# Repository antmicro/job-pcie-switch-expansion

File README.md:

# PCIe Switch Expansion for Antmicro Baseboard for NVIDIA Jetson Orin

Copyright (c) 2026 [Antmicro](https://www.antmicro.com)

## Overview

This project contains open hardware PCB design files for an expansion board compatible with Antmicro's [Baseboard for Jetson Orin](https://github.com/antmicro/jetson-orin-baseboard).
The design includes a PCIe 3.0 switch that expands the number of available PCIe ports by connecting multiple PCIe endpoint devices to a single PCIe root complex.
The expansion board includes an OCuLink Connector and two M.2 (key-M) slots intended for connecting additional storage solutions with optional RAID support.
Both M.2 slots support 2280 and 2242 M.2 NVMe drives.
The design files were prepared in KiCad 10.x.

## Key features

* Accessory compatible with expansion connector located on Antmicro Baseboard NVIDIA Jetson Orin
* Supports for 2280 and 2242 M.2 NVMe drives
* 1x M.2 key M PCIe x2 slot 
* 1x M.2 key M or 1x OCuLink Connector PCIe x2 (multiplexed lane)
* 100 x 60 mm (3.94 x 2.36 inch) PCB outline

## Project structure 

The main directory contains KiCad PCB project files, the LICENSE, and this README, and the img directory contains graphics for this README.

## Licensing

This project is published under the [Apache-2.0](LICENSE) license.

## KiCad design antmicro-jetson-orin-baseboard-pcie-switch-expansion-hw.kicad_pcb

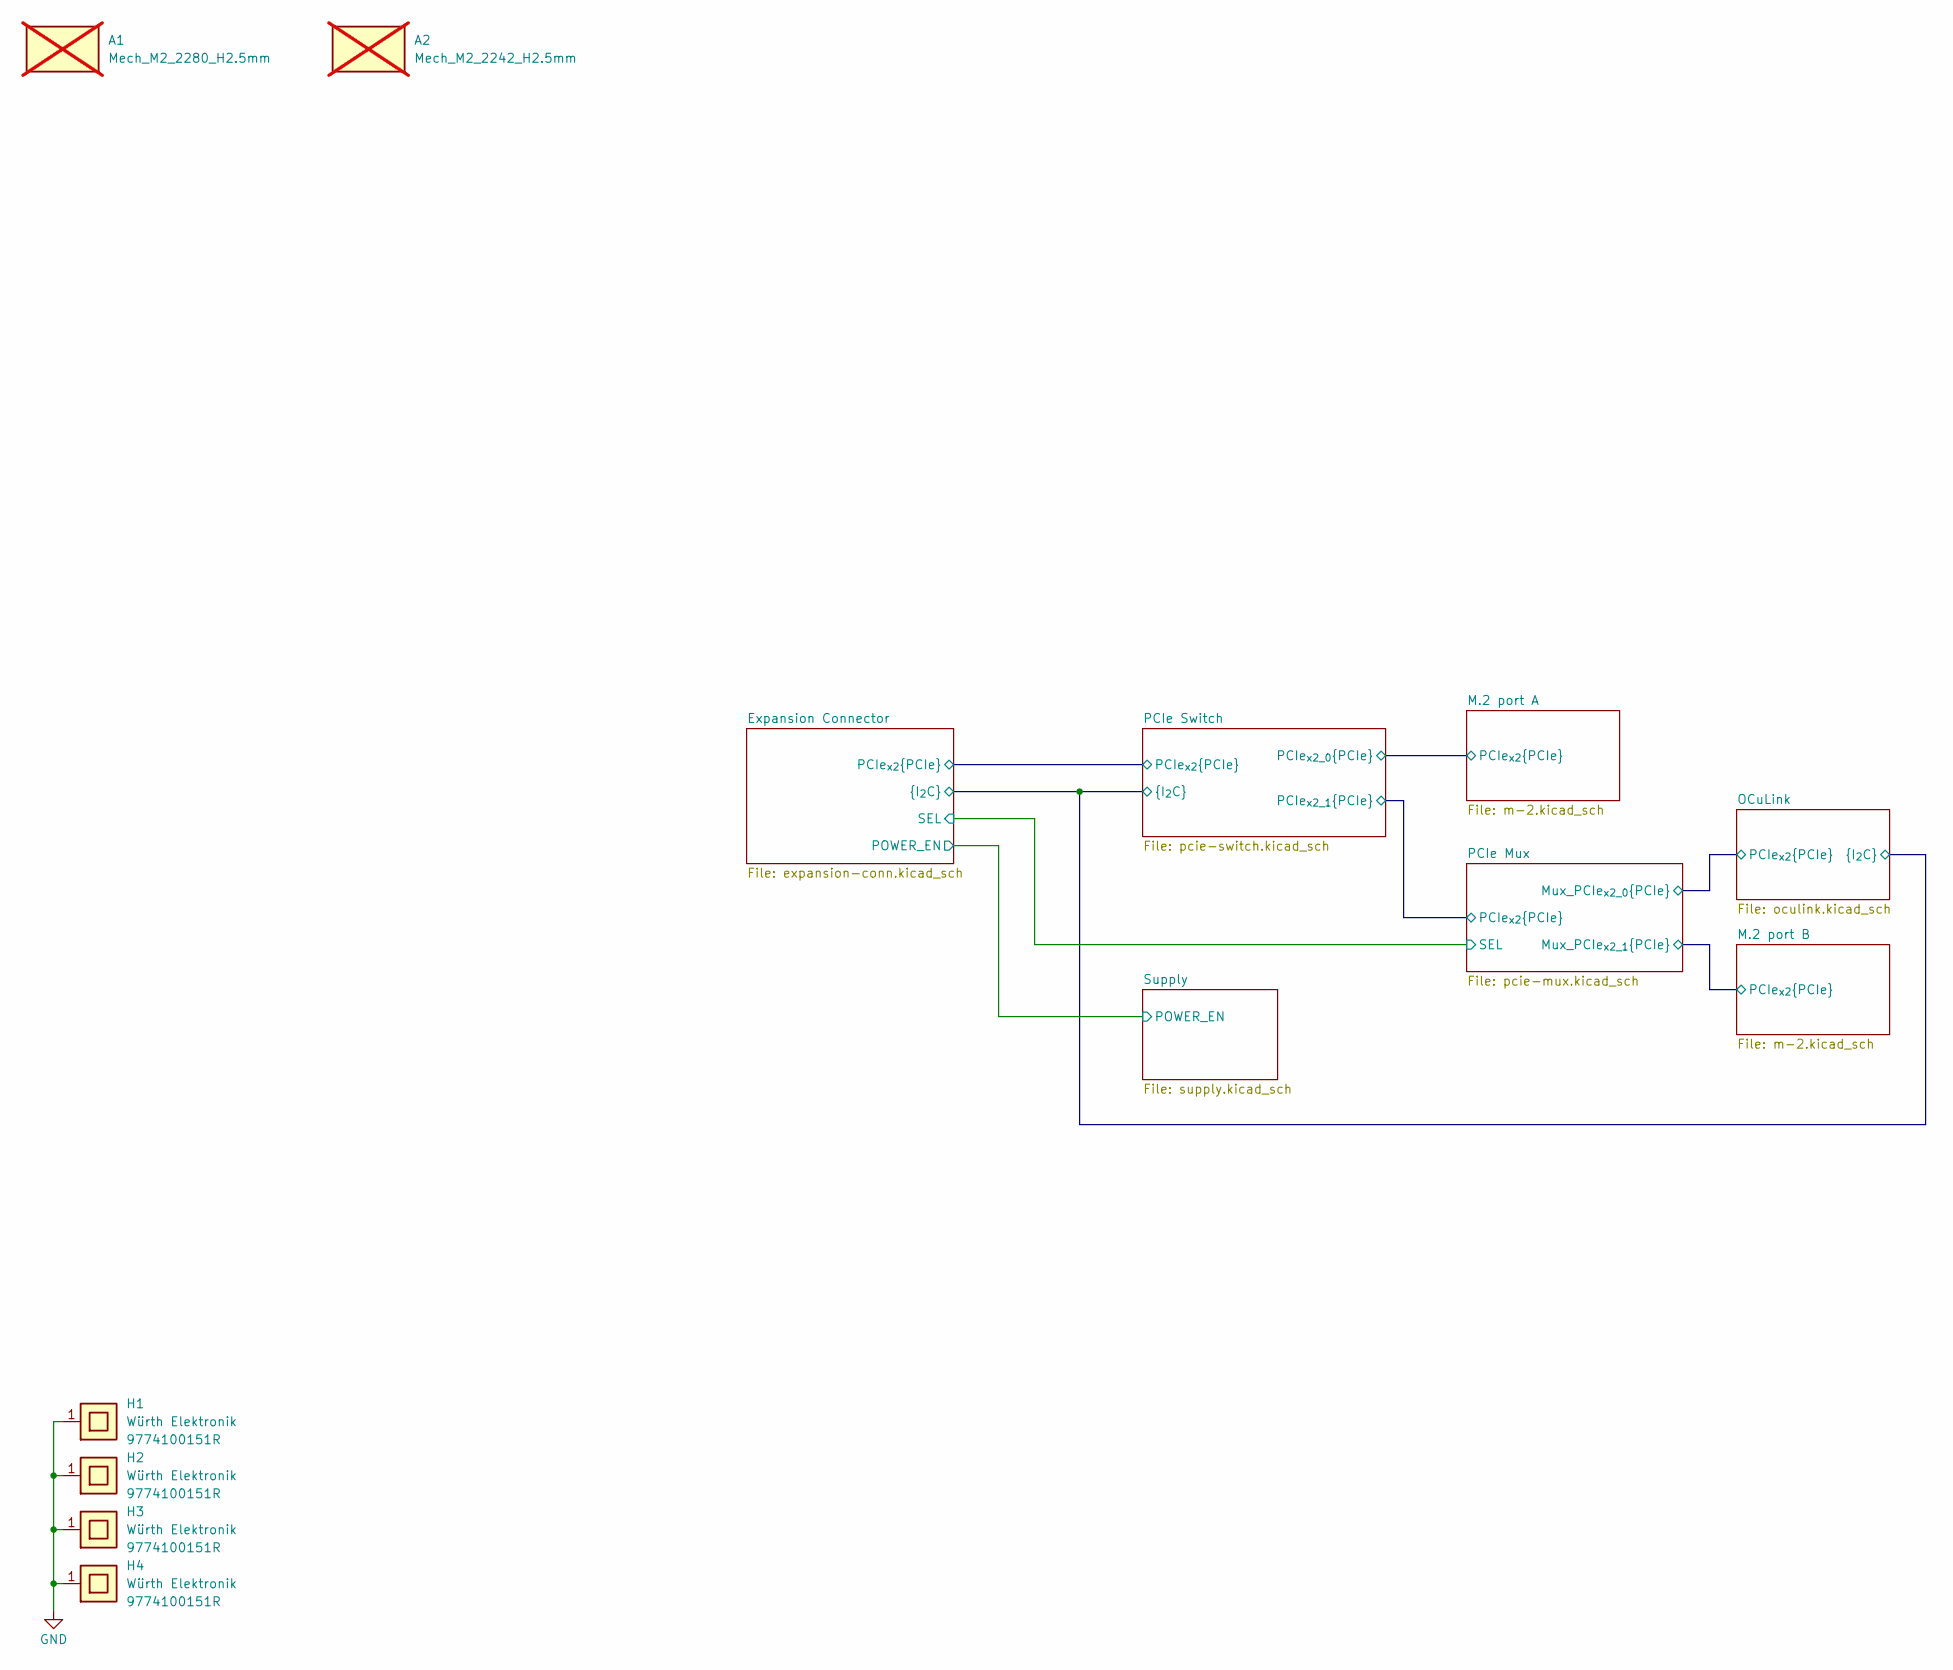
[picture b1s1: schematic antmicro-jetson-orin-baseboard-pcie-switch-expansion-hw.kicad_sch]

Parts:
A1: Mech_M2_2280_H2.5mm; not fitted
A2: Mech_M2_2242_H2.5mm; not fitted
H1, H2, H3, H4: Spacer_Drill3.7mm_H10mm_9774100151R; MPN 9774100151R

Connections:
GND: H1.1, H2.1, H3.1, H4.1; also elsewhere on the board

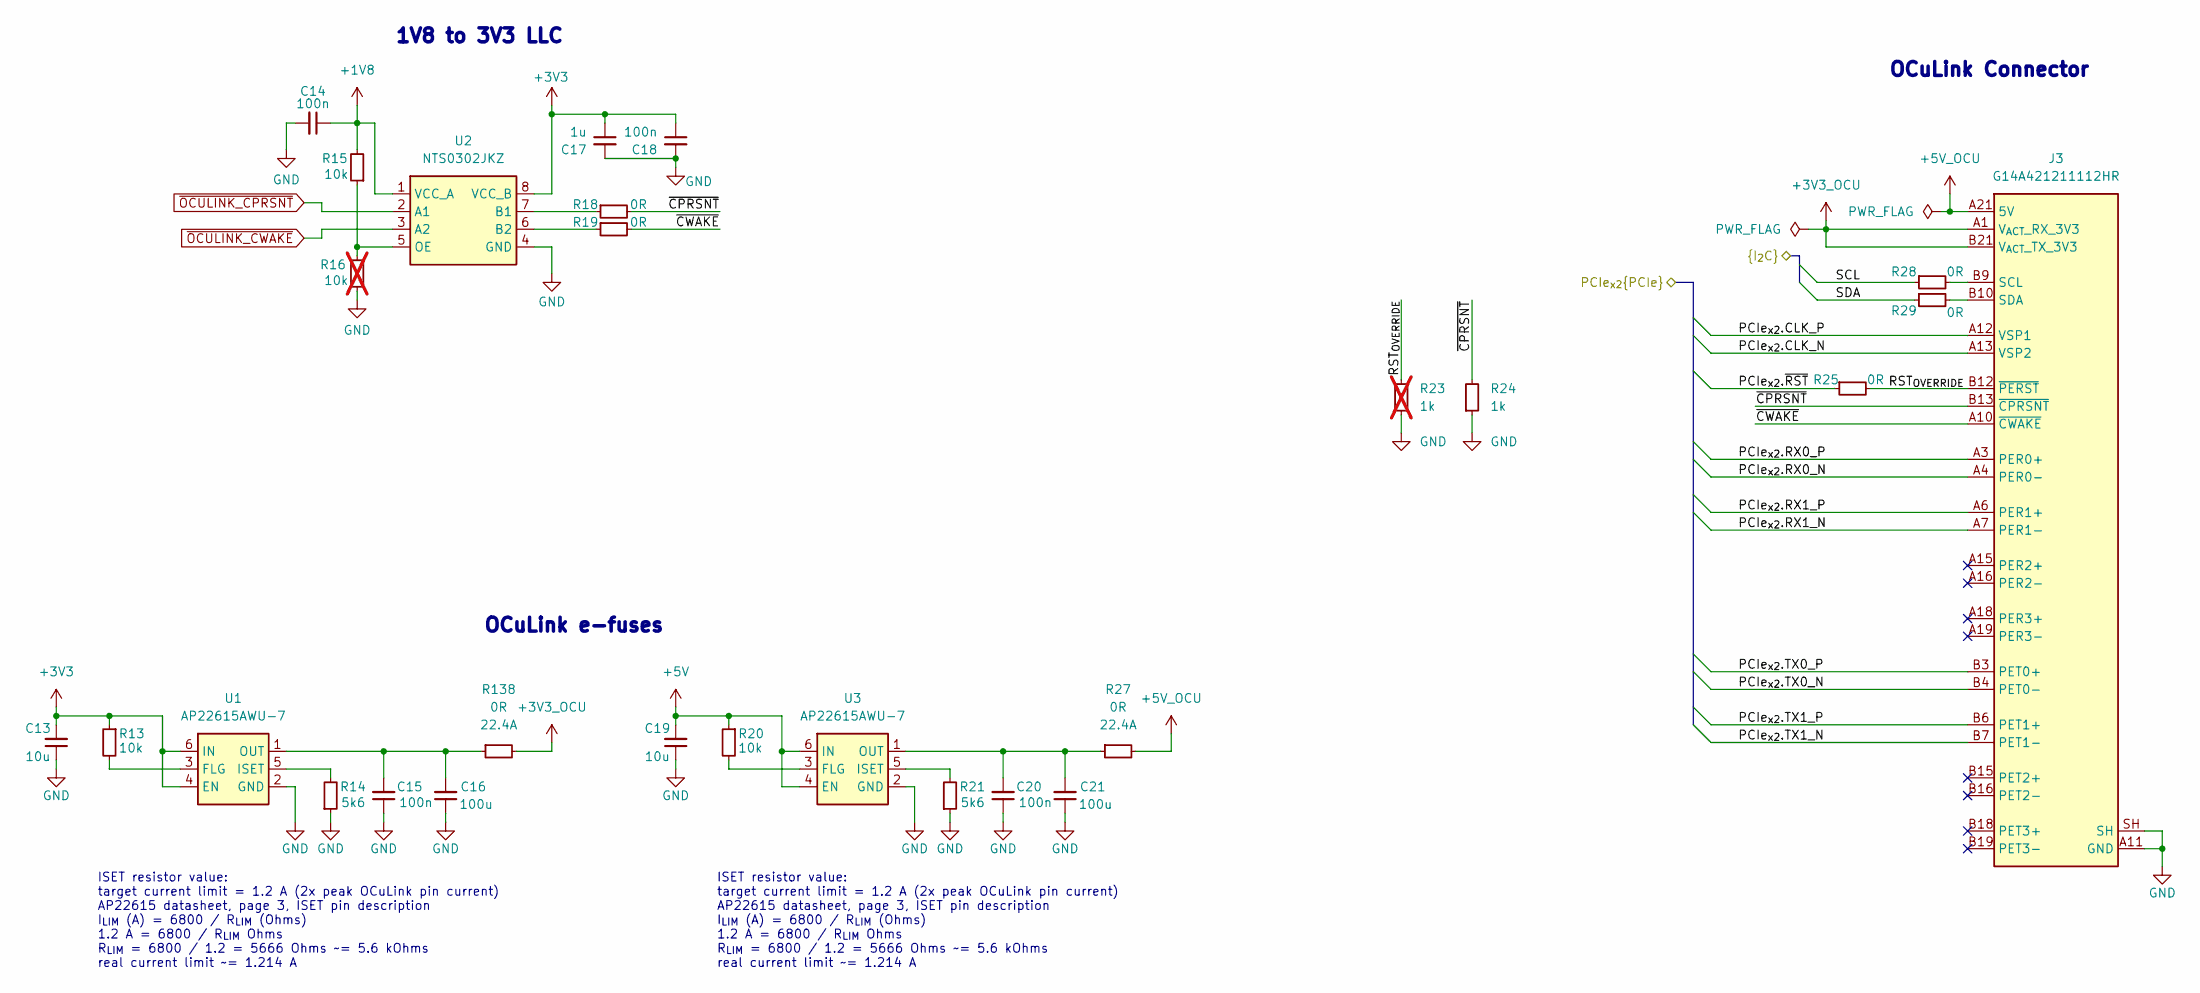
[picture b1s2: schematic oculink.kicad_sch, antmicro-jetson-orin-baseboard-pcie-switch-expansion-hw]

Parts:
C13, C19: C_10u_0402; C_0402_1005Metric; MPN CC0402MRX5R5BB106
C14, C15, C18, C20: C_100n_0402; C_0402_1005Metric; Voltage 50V; MPN GRM155R61H104KE14D
C16, C21: C_100u_0805; C_0805_2012Metric; MPN GRM21BR60J107ME15L
C17: C_1u_0402; C_0402_1005Metric; MPN C1005X6S1A105K050BC
J3: OCuLink_x4_Amphenol_G14A421211112HR; Amphenol_G14A421211112HR; MPN G14A421211112HR
R13, R15, R20: R_10k_0402; R_0402_1005Metric; Tolerance 1%; MPN CR0402-FX-1002GLF
R14, R21: R_5k6_0402; R_0402_1005Metric; Tolerance 1%; MPN CR0402-FX-5601GLF
R16: R_10k_0402; R_0402_1005Metric; Tolerance 1%; MPN CR0402-FX-1002GLF; not fitted
R18, R19, R25, R28, R29: R_0R_0402; R_0402_1005Metric; MPN ERJ2GE0R00X
R23: R_1k_0402; R_0402_1005Metric; Tolerance 1%; MPN CR0402-FX-1001GLF; not fitted
R24: R_1k_0402; R_0402_1005Metric; Tolerance 1%; MPN CR0402-FX-1001GLF
R27, R138: R_0R_22.4A_0603; R_0603_1608Metric; Tolerance template_tolerance; MPN PMR03EZPJ000
U1, U3: TSOT23-6; MPN AP22615AWU-7
U2: NTS0302JKZ; X2SON8_1.4x1x0.32mm_P0.35mm; MPN NTS0302JKZ

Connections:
+1V8: C14.1, R15.2, U2.1 (VCC_A); also elsewhere on the board
+3V3: C13.2, C17.1, C18.1, R13.1, U1.4 (EN), U1.6 (IN), U2.8 (VCC_B); also elsewhere on the board
+3V3_OCU: J3.A1 (V_{ACT}_RX_3V3), J3.B21 (V_{ACT}_TX_3V3), R138.2
+5V: C19.2, R20.1, U3.4 (EN), U3.6 (IN); also elsewhere on the board
+5V_OCU: J3.A21 (5V), J3.B1 (5V), R27.2
/Expansion Connector/SCL: R28.1; also elsewhere on the board
/Expansion Connector/SDA: R29.1; also elsewhere on the board
/OCuLink/PCIe_{x2}.CLK_N: J3.A13 (VSP2); also elsewhere on the board
/OCuLink/PCIe_{x2}.CLK_P: J3.A12 (VSP1); also elsewhere on the board
/OCuLink/PCIe_{x2}.RX0_N: J3.A4 (PER0-); also elsewhere on the board
/OCuLink/PCIe_{x2}.RX0_P: J3.A3 (PER0+); also elsewhere on the board
/OCuLink/PCIe_{x2}.RX1_N: J3.A7 (PER1-); also elsewhere on the board
/OCuLink/PCIe_{x2}.RX1_P: J3.A6 (PER1+); also elsewhere on the board
/OCuLink/PCIe_{x2}.TX0_N: J3.B4 (PET0-); also elsewhere on the board
/OCuLink/PCIe_{x2}.TX0_P: J3.B3 (PET0+); also elsewhere on the board
/OCuLink/PCIe_{x2}.TX1_N: J3.B7 (PET1-); also elsewhere on the board
/OCuLink/PCIe_{x2}.TX1_P: J3.B6 (PET1+); also elsewhere on the board
/OCuLink/PCIe_{x2}.~RST: R25.1; also elsewhere on the board
/OCuLink/RST_{OVERRIDE}: J3.B12 (~PERST), R23.2, R25.2
/OCuLink/~CPRSNT: J3.B13 (~CPRSNT), R18.2, R24.2
/OCuLink/~CWAKE: J3.A10 (~CWAKE), R19.2
GND: C13.1, C14.2, C15.1, C16.1, C17.2, C18.2, C19.1, C20.1, C21.1, J3.A2 (GND), J3.A5 (GND), J3.A8 (GND), J3.A11 (GND), J3.A14 (GND), J3.A17 (GND), J3.A20 (GND), J3.B2 (GND), J3.B5 (GND), J3.B8 (GND), J3.B11 (GND), J3.B14 (GND), J3.B17 (GND), J3.B20 (GND), J3.SH, R14.1, R16.1, R21.1, R23.1, R24.1, U1.2 (GND), U2.4 (GND), U3.2 (GND); also elsewhere on the board
unnamed: J3.B9 (SCL), R28.2
unnamed: J3.B10 (SDA), R29.2
unnamed: R13.2, U1.3 (FLG)
unnamed: R14.2, U1.5 (ISET)
unnamed: C15.2, C16.2, R138.1, U1.1 (OUT)
unnamed: R18.1, U2.7 (B1)
unnamed: R19.1, U2.6 (B2)
unnamed: R15.1, R16.2, U2.5 (OE)
unnamed: R20.2, U3.3 (FLG)
unnamed: R21.2, U3.5 (ISET)
unnamed: C20.2, C21.2, R27.1, U3.1 (OUT)
~OCULINK_CPRSNT: U2.2 (A1); also elsewhere on the board
~OCULINK_CWAKE: U2.3 (A2); also elsewhere on the board

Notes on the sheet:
ISET resistor value: target current limit = 1.2 A (2x peak OCuLink pin current) AP22615 datasheet, page 3, ISET pin description I_{LIM} (A) = 6800 / R_{LIM} (Ohms) 1.2 A = 6800 / R_{LIM} Ohms R_{LIM} = 6800 / 1.2 = 5666 Ohms ~= 5.6 kOhms real current limit ~= 1.214 A
OCuLink e-fuses
1V8 to 3V3 LLC
OCuLink Connector

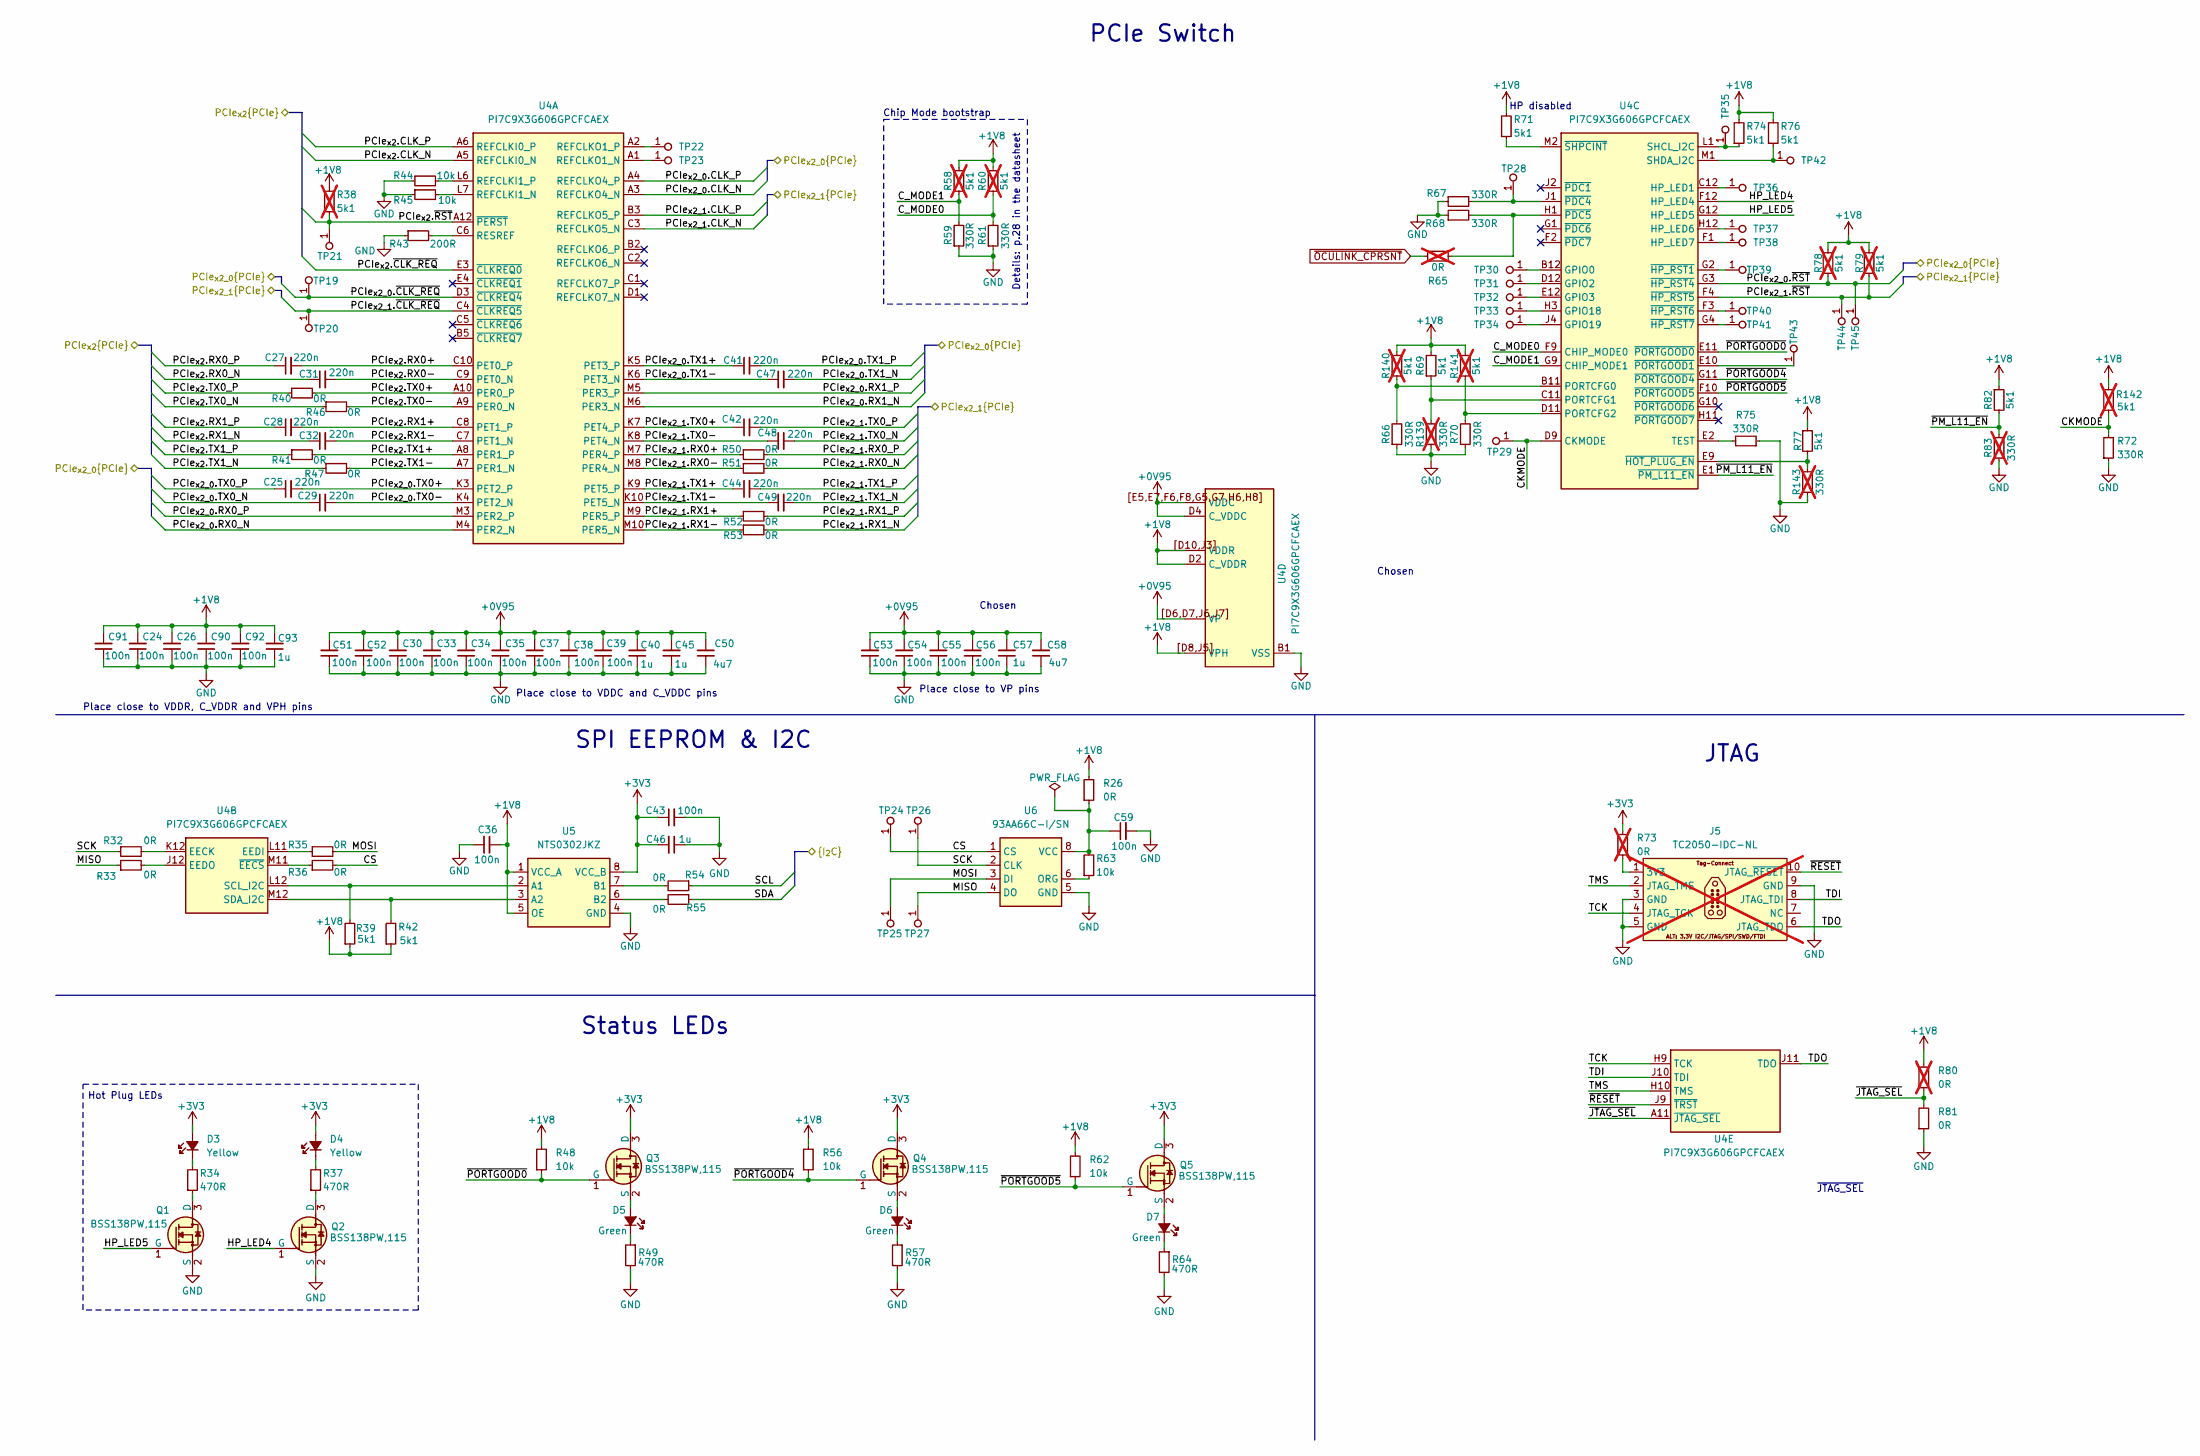
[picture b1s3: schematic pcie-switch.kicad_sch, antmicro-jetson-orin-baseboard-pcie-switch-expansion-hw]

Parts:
C24, C26, C30, C33, C34, C35, C36, C37, C38, C39, C43, C51, C52, C53, C54, C55, C56, C59, C90, C91, C92: C_100n_0402; C_0402_1005Metric; Voltage 50V; MPN GRM155R61H104KE14D
C25, C27, C28, C29, C31, C32, C41, C42, C44, C47, C48, C49: C_220n_0402; C_0402_1005Metric; MPN CC0402KRX5R6BB224
C40, C45, C46, C57, C93: C_1u_0402; C_0402_1005Metric; MPN C1005X6S1A105K050BC
C50, C58: C_4u7_25V_0402; C_0402_1005Metric; Voltage 25V; MPN GRM155C61E475ME15J
D3, D4: LED_Y_0402_VLMY1500-GS08; LED_0402_1005Metric_Y; MPN VLMY1500-GS08
D5, D6, D7: LED_G_0603_LG_L29K-G2J1-24-Z; LED_0603_1608Metric_G; MPN LG L29K-G2J1-24-Z
J5: Tag-Connect_TC2050-IDC-NL_2x5_P1.27mm; MPN TC2050-IDC-NL; not fitted
Q1, Q2, Q3, Q4, Q5: BSS138PW,115; SC70-3; MPN BSS138PW,115
R26, R32, R33, R35, R36, R40, R41, R46, R47, R50, R51, R52, R53, R54, R55, R81: R_0R_0402; R_0402_1005Metric; MPN ERJ2GE0R00X
R34, R37, R49, R57, R64: R_470R_0402; R_0402_1005Metric; Tolerance 1%; MPN CR0402-FX-4700GLF
R38, R58, R60, R78, R79, R140, R141, R142: R_5k1_0402; R_0402_1005Metric; Tolerance 1%; MPN CR0402-FX-5101GLF; not fitted
R39, R42, R69, R71, R74, R76, R77, R82: R_5k1_0402; R_0402_1005Metric; Tolerance 1%; MPN CR0402-FX-5101GLF
R43: R_200R_0402; R_0402_1005Metric; Tolerance 1%; MPN CR0402-FX-2000GLF
R44, R45, R48, R56, R62, R63: R_10k_0402; R_0402_1005Metric; Tolerance 1%; MPN CR0402-FX-1002GLF
R59, R61, R66, R67, R68, R70, R72, R75: R_330R_0402; R_0402_1005Metric; Tolerance 1%; MPN CR0402-FX-3300GLF
R65, R73, R80: R_0R_0402; R_0402_1005Metric; MPN ERJ2GE0R00X; not fitted
R83, R139, R143: R_330R_0402; R_0402_1005Metric; Tolerance 1%; MPN CR0402-FX-3300GLF; not fitted
TP19, TP20, TP21, TP22, TP23, TP28, TP29, TP30, TP31, TP32, TP33, TP34, TP35, TP36, TP37, TP38, TP39, TP40, TP41, TP42, TP43, TP44, TP45: TP_1mm_SMD; TP_SMD_1mm
TP24, TP25, TP26, TP27: TP_0.75mm_SMD; TP_SMD_0.75mm
U4: PI7C9X3G606GP; BGA-144_10x10mm_Layout12x12_P0.8mm; MPN PI7C9X3G606GPCFCAEX
U5: NTS0302JKZ; X2SON8_1.4x1x0.32mm_P0.35mm; MPN NTS0302JKZ
U6: 93AA66C_SOIC; SOIC-8_3.9x4.9x1.75mm_P1.27mm; MPN 93AA66C-I/SN

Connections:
+0V95: C30.2, C33.2, C34.2, C35.2, C37.2, C38.2, C39.2, C40.2, C45.2, C50.2, C51.2, C52.2, C53.2, C54.2, C55.2, C56.2, C57.2, C58.2, U4.D4 (C_VDDC), U4.D6 (VP), U4.D7 (VP), U4.E5 (VDDC), U4.E7 (VDDC), U4.F6 (VDDC), U4.F8 (VDDC), U4.G5 (VDDC), U4.G7 (VDDC), U4.H6 (VDDC), U4.H8 (VDDC), U4.J6 (VP), U4.J7 (VP), U4.[D6,D7,J6,J7] (VP), U4.[E5,E7,F6,F8,G5,G7,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 (VDDC); also elsewhere on the board
+1V8: C24.2, C26.2, C36.1, C90.2, C91.2, C92.2, C93.2, R26.2, R38.2, R39.1, R42.1, R48.2, R56.2, R58.2, R60.2, R62.2, R69.2, R71.2, R74.2, R76.2, R77.1, R78.1, R79.1, R80.2, R82.1, R140.2, R141.2, R142.1, U4.D2 (C_VDDR), U4.D8 (VPH), U4.D10 (VDDR), U4.J3 (VDDR), U4.J5 (VPH), U4.[D8,J5] (VPH), U4.[D10,J3] (VDDR), U5.1 (VCC_A), U5.5 (OE); also elsewhere on the board
+3V3: C43.1, C46.2, D3.2 (A), D4.2 (A), Q3.3 (D), Q4.3 (D), Q5.3 (D), R73.2, U5.8 (VCC_B); also elsewhere on the board
/Expansion Connector/PCIe_{x2}.CLK_N: U4.A5 (REFCLKI0_N); also elsewhere on the board
/Expansion Connector/PCIe_{x2}.CLK_P: U4.A6 (REFCLKI0_P); also elsewhere on the board
/Expansion Connector/PCIe_{x2}.RX0_N: C31.1; also elsewhere on the board
/Expansion Connector/PCIe_{x2}.RX0_P: C27.1; also elsewhere on the board
/Expansion Connector/PCIe_{x2}.RX1_N: C32.1; also elsewhere on the board
/Expansion Connector/PCIe_{x2}.RX1_P: C28.1; also elsewhere on the board
/Expansion Connector/PCIe_{x2}.TX0_N: R46.1; also elsewhere on the board
/Expansion Connector/PCIe_{x2}.TX0_P: R40.1; also elsewhere on the board
/Expansion Connector/PCIe_{x2}.TX1_N: R47.1; also elsewhere on the board
/Expansion Connector/PCIe_{x2}.TX1_P: R41.1; also elsewhere on the board
/Expansion Connector/PCIe_{x2}.~CLK_REQ: U4.E3 (~CLKREQ0); also elsewhere on the board
/Expansion Connector/PCIe_{x2}.~RST: R38.1, TP21.1 (1_1), U4.A12 (~PERST); also elsewhere on the board
/Expansion Connector/SCL: R54.1; also elsewhere on the board
/Expansion Connector/SDA: R55.1; also elsewhere on the board
/M.2 port A/PCIe_{x2}.CLK_N: U4.A3 (REFCLKO4_N); also elsewhere on the board
/M.2 port A/PCIe_{x2}.CLK_P: U4.A4 (REFCLKO4_P); also elsewhere on the board
/M.2 port A/PCIe_{x2}.RX0_N: U4.M4 (PER2_N); also elsewhere on the board
/M.2 port A/PCIe_{x2}.RX0_P: U4.M3 (PER2_P); also elsewhere on the board
/M.2 port A/PCIe_{x2}.RX1_N: U4.M6 (PER3_N); also elsewhere on the board
/M.2 port A/PCIe_{x2}.RX1_P: U4.M5 (PER3_P); also elsewhere on the board
/M.2 port A/PCIe_{x2}.TX0_N: C29.1; also elsewhere on the board
/M.2 port A/PCIe_{x2}.TX0_P: C25.1; also elsewhere on the board
/M.2 port A/PCIe_{x2}.TX1_N: C47.2; also elsewhere on the board
/M.2 port A/PCIe_{x2}.TX1_P: C41.2; also elsewhere on the board
/M.2 port A/PCIe_{x2}.~CLK_REQ: TP19.1 (1_1), U4.D3 (~CLKREQ4); also elsewhere on the board
/M.2 port A/PCIe_{x2}.~RST: R78.2, TP45.1 (1_1), U4.G3 (~HP_RST4); also elsewhere on the board
/PCIe Mux/PCIe_{x2}.CLK_N: U4.C3 (REFCLKO5_N); also elsewhere on the board
/PCIe Mux/PCIe_{x2}.CLK_P: U4.B3 (REFCLKO5_P); also elsewhere on the board
/PCIe Mux/PCIe_{x2}.RX0_N: R51.2; also elsewhere on the board
/PCIe Mux/PCIe_{x2}.RX0_P: R50.2; also elsewhere on the board
/PCIe Mux/PCIe_{x2}.RX1_N: R53.2; also elsewhere on the board
/PCIe Mux/PCIe_{x2}.RX1_P: R52.2; also elsewhere on the board
/PCIe Mux/PCIe_{x2}.TX0_N: C48.2; also elsewhere on the board
/PCIe Mux/PCIe_{x2}.TX0_P: C42.2; also elsewhere on the board
/PCIe Mux/PCIe_{x2}.TX1_N: C49.2; also elsewhere on the board
/PCIe Mux/PCIe_{x2}.TX1_P: C44.2; also elsewhere on the board
/PCIe Mux/PCIe_{x2}.~CLK_REQ: TP20.1 (1_1), U4.C4 (~CLKREQ5); also elsewhere on the board
/PCIe Mux/PCIe_{x2}.~RST: R79.2, TP44.1 (1_1), U4.F4 (~HP_RST5); also elsewhere on the board
/PCIe Switch/CKMODE: R72.2, R142.2, TP29.1 (1_1), U4.D9 (CKMODE)
/PCIe Switch/CS: R36.2, TP24.1 (1_1), U6.1 (CS)
/PCIe Switch/C_MODE0: R60.1, R61.2, U4.F9 (CHIP_MODE0)
/PCIe Switch/C_MODE1: R58.1, R59.2, U4.G9 (CHIP_MODE1)
/PCIe Switch/HP_LED4: Q2.1 (G), U4.F12 (HP_LED4)
/PCIe Switch/HP_LED5: Q1.1 (G), U4.G12 (HP_LED5)
/PCIe Switch/MISO: R33.1, TP27.1 (1_1), U6.4 (DO)
/PCIe Switch/MOSI: R35.2, TP25.1 (1_1), U6.3 (DI)
/PCIe Switch/PCIe_{x2_0}.TX0+: C25.2, U4.K3 (PET2_P)
/PCIe Switch/PCIe_{x2_0}.TX0-: C29.2, U4.K4 (PET2_N)
/PCIe Switch/PCIe_{x2_0}.TX1+: C41.1, U4.K5 (PET3_P)
/PCIe Switch/PCIe_{x2_0}.TX1-: C47.1, U4.K6 (PET3_N)
/PCIe Switch/PCIe_{x2_1}.RX0+: R50.1, U4.M7 (PER4_P)
/PCIe Switch/PCIe_{x2_1}.RX0-: R51.1, U4.M8 (PER4_N)
/PCIe Switch/PCIe_{x2_1}.RX1+: R52.1, U4.M9 (PER5_P)
/PCIe Switch/PCIe_{x2_1}.RX1-: R53.1, U4.M10 (PER5_N)
/PCIe Switch/PCIe_{x2_1}.TX0+: C42.1, U4.K7 (PET4_P)
/PCIe Switch/PCIe_{x2_1}.TX0-: C48.1, U4.K8 (PET4_N)
/PCIe Switch/PCIe_{x2_1}.TX1+: C44.1, U4.K9 (PET5_P)
/PCIe Switch/PCIe_{x2_1}.TX1-: C49.1, U4.K10 (PET5_N)
/PCIe Switch/PCIe_{x2}.RX0+: C27.2, U4.C10 (PET0_P)
/PCIe Switch/PCIe_{x2}.RX0-: C31.2, U4.C9 (PET0_N)
/PCIe Switch/PCIe_{x2}.RX1+: C28.2, U4.C8 (PET1_P)
/PCIe Switch/PCIe_{x2}.RX1-: C32.2, U4.C7 (PET1_N)
/PCIe Switch/PCIe_{x2}.TX0+: R40.2, U4.A10 (PER0_P)
/PCIe Switch/PCIe_{x2}.TX0-: R46.2, U4.A9 (PER0_N)
/PCIe Switch/PCIe_{x2}.TX1+: R41.2, U4.A8 (PER1_P)
/PCIe Switch/PCIe_{x2}.TX1-: R47.2, U4.A7 (PER1_N)
/PCIe Switch/SCK: R32.1, TP26.1 (1_1), U6.2 (CLK)
/PCIe Switch/TCK: J5.4 (JTAG_TCK), U4.H9 (TCK)
/PCIe Switch/TDI: J5.8 (JTAG_TDI), U4.J10 (TDI)
/PCIe Switch/TDO: J5.6 (JTAG_TDO), U4.J11 (TDO)
/PCIe Switch/TMS: J5.2 (JTAG_TMS), U4.H10 (TMS)
/PCIe Switch/~JTAG_SEL: R80.1, R81.2, U4.A11 (~JTAG_SEL)
/PCIe Switch/~PM_L11_EN: R82.2, R83.1, U4.E1 (~PM_L11_EN)
/PCIe Switch/~PORTGOOD0: Q3.1 (G), R48.1, U4.E11 (~PORTGOOD0)
/PCIe Switch/~PORTGOOD4: Q4.1 (G), R56.1, U4.G11 (~PORTGOOD4)
/PCIe Switch/~PORTGOOD5: Q5.1 (G), R62.1, U4.F10 (~PORTGOOD5)
/PCIe Switch/~RESET: J5.10 (JTAG_~RESET), U4.J9 (~TRST)
GND: C24.1, C26.1, C30.1, C33.1, C34.1, C35.1, C36.2, C37.1, C38.1, C39.1, C40.1, C43.2, C45.1, C46.1, C50.1, C51.1, C52.1, C53.1, C54.1, C55.1, C56.1, C57.1, C58.1, C59.2, C90.1, C91.1, C92.1, C93.1, J5.3 (GND), J5.5 (GND), J5.9 (GND), Q1.2 (S), Q2.2 (S), R43.1, R44.1, R45.1, R49.2, R57.2, R59.1, R61.1, R64.2, R66.1, R67.1, R68.1, R70.1, R72.1, R75.1, R81.1, R83.2, R139.1, R143.1, U4.B1 (VSS), U4.B4 (VSS), U4.B6 (VSS), U4.B7 (VSS), U4.B8 (VSS), U4.B9 (VSS), U4.B10 (VSS), U4.D5 (VSS), U4.E6 (VSS), U4.E8 (VSS), U4.F5 (VSS), U4.F7 (VSS), U4.F11 (VSS), U4.G6 (VSS), U4.G8 (VSS), U4.H5 (VSS), U4.H7 (VSS), U4.J8 (VSS), U4.K2 (VSS), U4.K11 (VSS), U4.L3 (VSS), U4.L4 (VSS), U4.L5 (VSS), U4.L8 (VSS), U4.L9 (VSS), U4.L10 (VSS), U5.4 (GND), U6.5 (GND); also elsewhere on the board
unnamed: D3.1 (C), R34.2
unnamed: D4.1 (C), R37.2
unnamed: D5.2 (A), Q3.2 (S)
unnamed: D5.1 (C), R49.1
unnamed: D6.2 (A), Q4.2 (S)
unnamed: D6.1 (C), R57.1
unnamed: D7.2 (A), Q5.2 (S)
unnamed: D7.1 (C), R64.1
unnamed: J5.1 (3V3), R73.1
unnamed: Q1.3 (D), R34.1
unnamed: Q2.3 (D), R37.1
unnamed: R45.2, U4.L7 (REFCLKI1_N)
unnamed: R44.2, U4.L6 (REFCLKI1_P)
unnamed: TP23.1 (1_1), U4.A1 (REFCLKO1_N)
unnamed: TP22.1 (1_1), U4.A2 (REFCLKO1_P)
unnamed: R43.2, U4.C6 (RESREF)
unnamed: R32.2, U4.K12 (EECK)
unnamed: R35.1, U4.L11 (EEDI)
unnamed: R33.2, U4.J12 (EEDO)
unnamed: R39.2, U4.L12 (SCL_I2C), U5.2 (A1)
unnamed: R42.2, U4.M12 (SDA_I2C), U5.3 (A2)
unnamed: R36.1, U4.M11 (~EECS)
unnamed: TP30.1 (1_1), U4.B12 (GPIO0)
unnamed: TP31.1 (1_1), U4.D12 (GPIO2)
unnamed: TP32.1 (1_1), U4.E12 (GPIO3)
unnamed: TP33.1 (1_1), U4.H3 (GPIO18)
unnamed: TP34.1 (1_1), U4.J4 (GPIO19)
unnamed: TP36.1 (1_1), U4.C12 (HP_LED1)
unnamed: TP37.1 (1_1), U4.H12 (HP_LED6)
unnamed: TP38.1 (1_1), U4.F1 (HP_LED7)
unnamed: R66.2, R140.1, U4.B11 (PORTCFG0)
unnamed: R69.1, R139.2, U4.C11 (PORTCFG1)
unnamed: R70.2, R141.1, U4.D11 (PORTCFG2)
unnamed: R74.1, TP35.1 (1_1), U4.L1 (SHCL_I2C)
unnamed: R76.1, TP42.1 (1_1), U4.M1 (SHDA_I2C)
unnamed: R75.2, U4.E2 (TEST)
unnamed: R77.2, R143.2, U4.E9 (~HOT_PLUG_EN)
unnamed: TP39.1 (1_1), U4.G2 (~HP_RST1)
unnamed: TP40.1 (1_1), U4.F3 (~HP_RST6)
unnamed: TP41.1 (1_1), U4.G4 (~HP_RST7)
unnamed: R67.2, TP28.1 (1_1), U4.J1 (~PDC4)
unnamed: R65.2, R68.2, U4.H1 (~PDC5)
unnamed: TP43.1 (1_1), U4.E10 (~PORTGOOD1)
unnamed: R71.1, U4.M2 (~SHPCINT)
unnamed: R54.2, U5.7 (B1)
unnamed: R55.2, U5.6 (B2)
unnamed: R63.1, U6.6 (ORG)
unnamed: C59.1, R26.1, R63.2, U6.8 (VCC)
~OCULINK_CPRSNT: R65.1; also elsewhere on the board

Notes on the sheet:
PCIe Switch
~{JTAG_SEL}
Hot Plug LEDs
Place close to VDDR, C_VDDR and VPH pins
Place close to VP pins
HP disabled
JTAG
Details: p.28 in the datasheet
Place close to VDDC and C_VDDC pins
Chosen
Status LEDs
SPI EEPROM & I2C
Chip Mode bootstrap

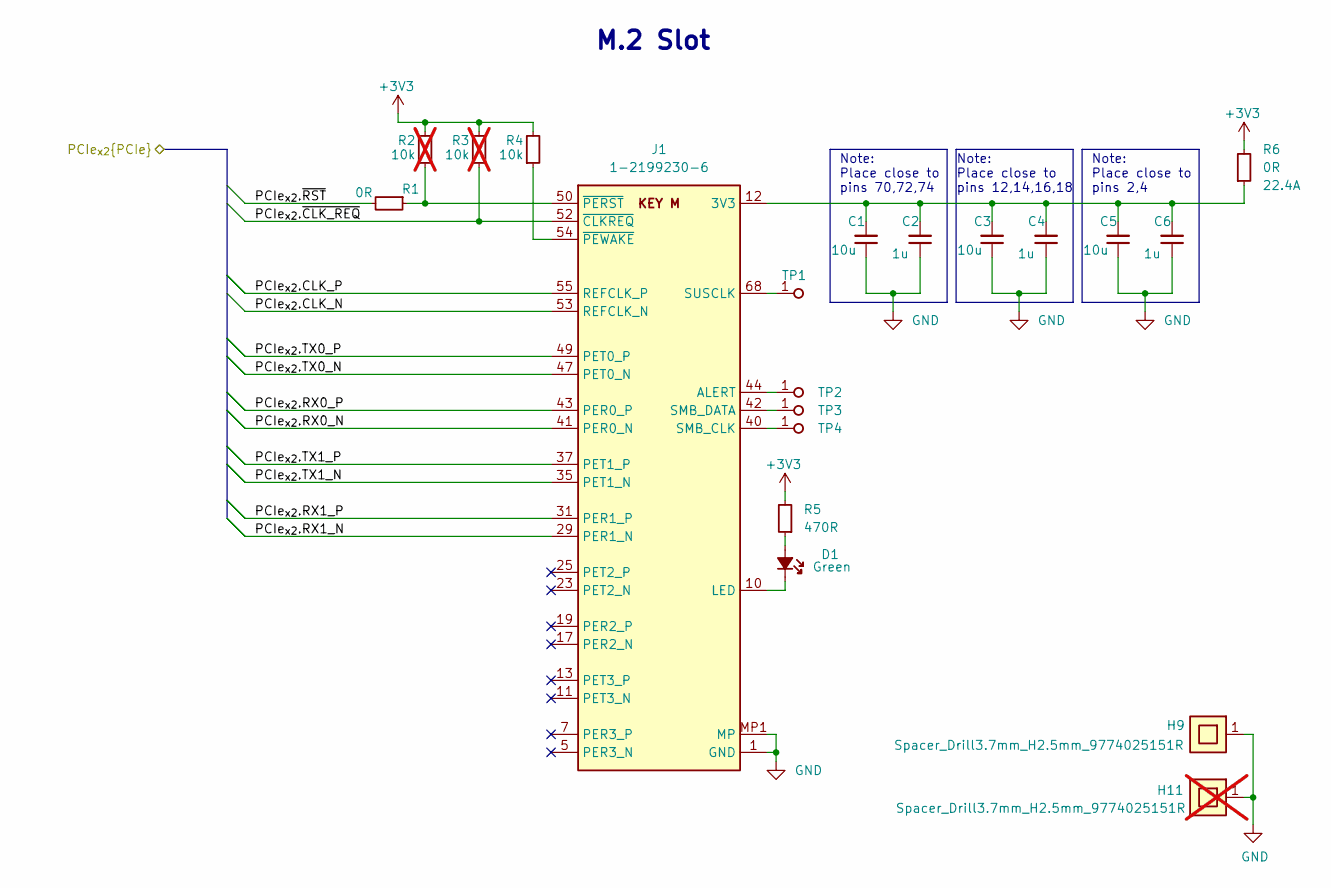
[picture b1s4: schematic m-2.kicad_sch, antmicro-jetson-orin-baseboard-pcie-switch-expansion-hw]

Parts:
C1, C3, C5: C_10u_0402; C_0402_1005Metric; MPN CC0402MRX5R5BB106
C2, C4, C6: C_1u_0402; C_0402_1005Metric; MPN C1005X6S1A105K050BC
D1: LED_G_0603_KP-1608CGCK; LED_0603_1608Metric_G; MPN KP-1608CGCK
H9: Spacer_Drill3.7mm_H2.5mm_9774025151R; MPN 9774025151R
H11: Spacer_Drill3.7mm_H2.5mm_9774025151R; MPN 9774025151R; not fitted
J1: Bus_M.2_1-2199230-6; Bus_M.2_Socket_Key_M_TE_1-2199230-6; MPN 1-2199230-6
R1: R_0R_0402; R_0402_1005Metric; MPN ERJ2GE0R00X
R2, R3: R_10k_0402; R_0402_1005Metric; Tolerance 1%; MPN CR0402-FX-1002GLF; not fitted
R4: R_10k_0402; R_0402_1005Metric; Tolerance 1%; MPN CR0402-FX-1002GLF
R5: R_470R_0402; R_0402_1005Metric; Tolerance 1%; MPN CR0402-FX-4700GLF
R6: R_0R_22.4A_0603; R_0603_1608Metric; Tolerance template_tolerance; MPN PMR03EZPJ000
TP1, TP2, TP3, TP4: TP_0.75mm_SMD; TP_SMD_0.75mm

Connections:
+3V3: R2.2, R3.2, R4.2, R5.2, R6.2; also elsewhere on the board
/M.2 port A/PCIe_{x2}.CLK_N: J1.53 (REFCLK_N); also elsewhere on the board
/M.2 port A/PCIe_{x2}.CLK_P: J1.55 (REFCLK_P); also elsewhere on the board
/M.2 port A/PCIe_{x2}.RX0_N: J1.41 (PER0_N); also elsewhere on the board
/M.2 port A/PCIe_{x2}.RX0_P: J1.43 (PER0_P); also elsewhere on the board
/M.2 port A/PCIe_{x2}.RX1_N: J1.29 (PER1_N); also elsewhere on the board
/M.2 port A/PCIe_{x2}.RX1_P: J1.31 (PER1_P); also elsewhere on the board
/M.2 port A/PCIe_{x2}.TX0_N: J1.47 (PET0_N); also elsewhere on the board
/M.2 port A/PCIe_{x2}.TX0_P: J1.49 (PET0_P); also elsewhere on the board
/M.2 port A/PCIe_{x2}.TX1_N: J1.35 (PET1_N); also elsewhere on the board
/M.2 port A/PCIe_{x2}.TX1_P: J1.37 (PET1_P); also elsewhere on the board
/M.2 port A/PCIe_{x2}.~CLK_REQ: J1.52 (~CLKREQ), R3.1; also elsewhere on the board
/M.2 port A/PCIe_{x2}.~RST: R1.2; also elsewhere on the board
GND: C1.1, C2.1, C3.1, C4.1, C5.1, C6.1, H9.1, H11.1, J1.1 (GND), J1.3 (GND), J1.9 (GND), J1.15 (GND), J1.21 (GND), J1.27 (GND), J1.33 (GND), J1.39 (GND), J1.45 (GND), J1.51 (GND), J1.57 (GND), J1.71 (GND), J1.73 (GND), J1.75 (GND), J1.MP1 (MP), J1.MP2 (MP); also elsewhere on the board
unnamed: C1.2, C2.2, C3.2, C4.2, C5.2, C6.2, J1.2 (3V3), J1.4 (3V3), J1.12 (3V3), J1.14 (3V3), J1.16 (3V3), J1.18 (3V3), J1.70 (3V3), J1.72 (3V3), J1.74 (3V3), R6.1
unnamed: D1.2 (A), R5.1
unnamed: D1.1 (C), J1.10 (LED)
unnamed: J1.44 (ALERT), TP2.1 (1_1)
unnamed: J1.40 (SMB_CLK), TP4.1 (1_1)
unnamed: J1.42 (SMB_DATA), TP3.1 (1_1)
unnamed: J1.68 (SUSCLK), TP1.1 (1_1)
unnamed: J1.50 (~PERST), R1.1, R2.1
unnamed: J1.54 (~PEWAKE), R4.1

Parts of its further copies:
C7, C9, C11: C_10u_0402; C_0402_1005Metric; MPN CC0402MRX5R5BB106
C8, C10, C12: C_1u_0402; C_0402_1005Metric; MPN C1005X6S1A105K050BC
D2: LED_G_0603_KP-1608CGCK; LED_0603_1608Metric_G; MPN KP-1608CGCK
H10: Spacer_Drill3.7mm_H2.5mm_9774025151R; MPN 9774025151R
H12: Spacer_Drill3.7mm_H2.5mm_9774025151R; MPN 9774025151R; not fitted
J2: Bus_M.2_1-2199230-6; Bus_M.2_Socket_Key_M_TE_1-2199230-6; MPN 1-2199230-6
R7: R_0R_0402; R_0402_1005Metric; MPN ERJ2GE0R00X
R8, R9: R_10k_0402; R_0402_1005Metric; Tolerance 1%; MPN CR0402-FX-1002GLF; not fitted
R10: R_10k_0402; R_0402_1005Metric; Tolerance 1%; MPN CR0402-FX-1002GLF
R11: R_470R_0402; R_0402_1005Metric; Tolerance 1%; MPN CR0402-FX-4700GLF
R12: R_0R_22.4A_0603; R_0603_1608Metric; Tolerance template_tolerance; MPN PMR03EZPJ000
TP5, TP6, TP7, TP8: TP_0.75mm_SMD; TP_SMD_0.75mm

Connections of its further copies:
+3V3: R8.2, R9.2, R10.2, R11.2, R12.2; also elsewhere on the board
/M.2 port B/PCIe_{x2}.CLK_N: J2.53 (REFCLK_N); also elsewhere on the board
/M.2 port B/PCIe_{x2}.CLK_P: J2.55 (REFCLK_P); also elsewhere on the board
/M.2 port B/PCIe_{x2}.RX0_N: J2.41 (PER0_N); also elsewhere on the board
/M.2 port B/PCIe_{x2}.RX0_P: J2.43 (PER0_P); also elsewhere on the board
/M.2 port B/PCIe_{x2}.RX1_N: J2.29 (PER1_N); also elsewhere on the board
/M.2 port B/PCIe_{x2}.RX1_P: J2.31 (PER1_P); also elsewhere on the board
/M.2 port B/PCIe_{x2}.TX0_N: J2.47 (PET0_N); also elsewhere on the board
/M.2 port B/PCIe_{x2}.TX0_P: J2.49 (PET0_P); also elsewhere on the board
/M.2 port B/PCIe_{x2}.TX1_N: J2.35 (PET1_N); also elsewhere on the board
/M.2 port B/PCIe_{x2}.TX1_P: J2.37 (PET1_P); also elsewhere on the board
/M.2 port B/PCIe_{x2}.~CLK_REQ: J2.52 (~CLKREQ), R9.1; also elsewhere on the board
/M.2 port B/PCIe_{x2}.~RST: R7.2; also elsewhere on the board
GND: C7.1, C8.1, C9.1, C10.1, C11.1, C12.1, H10.1, H12.1, J2.1 (GND), J2.3 (GND), J2.9 (GND), J2.15 (GND), J2.21 (GND), J2.27 (GND), J2.33 (GND), J2.39 (GND), J2.45 (GND), J2.51 (GND), J2.57 (GND), J2.71 (GND), J2.73 (GND), J2.75 (GND), J2.MP1 (MP), J2.MP2 (MP); also elsewhere on the board
unnamed: C7.2, C8.2, C9.2, C10.2, C11.2, C12.2, J2.2 (3V3), J2.4 (3V3), J2.12 (3V3), J2.14 (3V3), J2.16 (3V3), J2.18 (3V3), J2.70 (3V3), J2.72 (3V3), J2.74 (3V3), R12.1
unnamed: D2.2 (A), R11.1
unnamed: D2.1 (C), J2.10 (LED)
unnamed: J2.44 (ALERT), TP6.1 (1_1)
unnamed: J2.40 (SMB_CLK), TP8.1 (1_1)
unnamed: J2.42 (SMB_DATA), TP7.1 (1_1)
unnamed: J2.68 (SUSCLK), TP5.1 (1_1)
unnamed: J2.50 (~PERST), R7.1, R8.1
unnamed: J2.54 (~PEWAKE), R10.1

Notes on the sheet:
Note: Place close to pins 2,4
M.2 Slot
Note: Place close to pins 12,14,16,18
Note: Place close to pins 70,72,74

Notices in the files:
parts and their libraries:
License: Apache-2.0
